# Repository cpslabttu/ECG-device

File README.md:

# ECG-device-TypeC
Created by: Dr. B. I. Morshed, Assoc. Prof., EECE, University of Memphis, Memphis TN USA.

If using this project files, please cite:

B. I. Morshed, "Ultra Low-power Inductively Coupled Wearable ECG Sensor Design with Inkjet Printed Dry Electrodes", National Radio Science Meeting, Boulder, CO, 2019.

B. I. Morshed, B. Harmon, M. S. Zaman, M. J. Rahman, S. Afroz, and M. Rahman, "Inkjet Printed Fully-passive Body-worn Wireless Sensors for Smart and Connected Community (SCC)", J. Low Power Electron. Appl., vol. 7, no. 4, article 26, pp. 1-21, Nov. 2017.

Sergi Consul-Pacareu, and Bashir I. Morshed, "Design and analysis of a novel wireless resistive analog passive sensor technique", IET Wireless Sensor Systems, vol. 8, no. 2, pp. 45-51, 2018.

B. Noroozi and B. I. Morshed, "PSC Optimization of 13.56-MHz Resistive Wireless Analog Passive Sensors", IEEE Trans. Microwave Theory and Techniques, vol. 65, no. 9, pp. 3548-3555, Sept. 2017.

For project related info, please visit: http://www.memphis.edu/esarp/nsf_scc/index.php

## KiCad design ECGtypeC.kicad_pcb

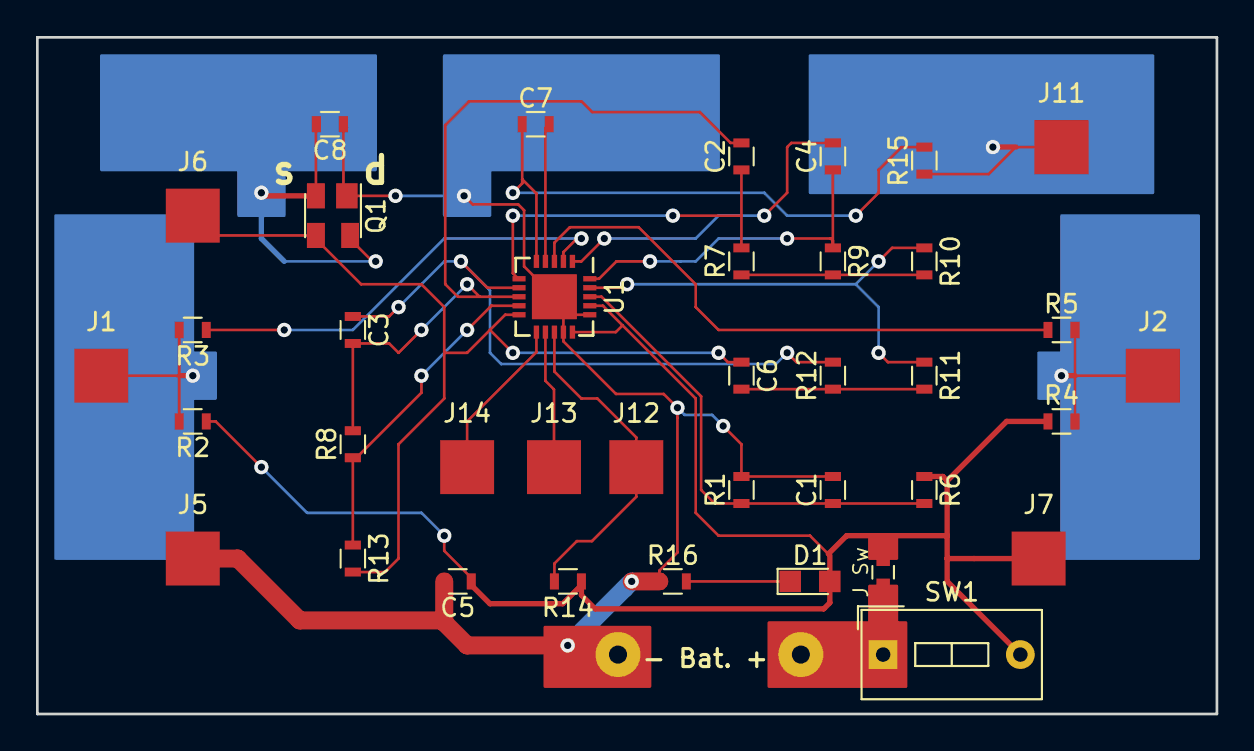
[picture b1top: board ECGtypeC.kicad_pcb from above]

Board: 2 copper layers, 65.5 x 37.6 mm, 39 parts (0 on the bottom side), 25 nets.

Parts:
- Bat. +: WireConnection_1mmDrill; WireConnection_1.00mmDrill
C1, C5: .1u; R_0603
C2, C4: .33u; R_0603
C3: 10n; R_0603
C6: .5n; R_0603
C7: 1n; R_0603
C8: 200p; R_0603
D1: LED_ALT; LED_0805
J1: L; Measurement_Point_Square-SMD-Pad_Big
J2: R; Measurement_Point_Square-SMD-Pad_Big
J5: Gnd; Measurement_Point_Square-SMD-Pad_Big
J6: Out; Measurement_Point_Square-SMD-Pad_Big
J7: Vdd; Measurement_Point_Square-SMD-Pad_Big
J11: D; Measurement_Point_Square-SMD-Pad_Big
J12: SDN; Measurement_Point_Square-SMD-Pad_Big
J13: LO+; Measurement_Point_Square-SMD-Pad_Big
J14: LO-; Measurement_Point_Square-SMD-Pad_Big
J Sw: C_0603_HandSoldering
Q1: 3SK263; SOT-143
R1, R2, R4, R6, R9, R10: 10M; R_0603
R3, R5: 180k; R_0603
R7: 1.4M; R_0603
R8: 100k; R_0603
R11, R12, R13: 1M; R_0603
R14: 10k; R_0603
R15: 300k; R_0603
R16: 1k; R_0603
SW1: SW_DIP_x01; SW_DIP_x1_W7.62mm_Slide
U1: AD8232; QFN-20-1EP_4x4mm_Pitch0.5mm

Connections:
0: C1.2, C5.2, C8.1, J5.1, Q1.1, R1.2, R16.1, U1.14, U1.16, U1.21
/LO+: J13.1, U1.12
/LO-: J14.1, U1.11
/SDN: J12.1, R14.2, U1.13
unnamed: C1.1, R1.1, R6.2, U1.18
unnamed: C2.1, R7.2, U1.6
unnamed: C2.2, C3.2, R8.2, U1.8
unnamed: C3.1, R12.2, U1.7
unnamed: C4.1, R9.1, U1.20
unnamed: C4.2, U1.1
unnamed: C5.1, D1.2, J7.1, R2.1, R4.1, R6.1, R14.1, SW1.2, U1.15, U1.17
unnamed: C6.1, J6.1, Q1.3, R13.2, U1.10
unnamed: C6.2, R11.2, R12.1
unnamed: C7.1, R15.2, U1.5
unnamed: C7.2, U1.4
unnamed: C8.2, Q1.2, Q1.4
unnamed: D1.1, R16.2
unnamed: J1.1, R2.2, R3.2
unnamed: J2.1, R4.2, R5.2
unnamed: J11.1, R15.1
unnamed: R3.1, U1.2
unnamed: R5.1, U1.3
unnamed: R10.1, R11.1, U1.19
unnamed: R7.1, R9.2, R10.2
unnamed: R8.1, R13.1, U1.9

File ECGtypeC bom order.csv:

Reference, Value, Footprint, DatasheetU1,AD8232ACPZ-R7,Housings_DFN_QFN:QFN-20-1EP_4x4mm_Pitch0.5mm,SW1,SW_DIP_x01,Buttons_Switches_THT:SW_DIP_x1_W7.62mm_Slide,C4,.33u,Resistors_SMD:R_0603,C3,10n,Resistors_SMD:R_0603,R9,10M,Resistors_SMD:R_0603,R7,1.4M,Resistors_SMD:R_0603,R10,10M,Resistors_SMD:R_0603,C2,.33u,Resistors_SMD:R_0603,R8,100k,Resistors_SMD:R_0603,R13,1M,Resistors_SMD:R_0603,C6,.5n,Resistors_SMD:R_0603,R12,1M,Resistors_SMD:R_0603,R11,1M,Resistors_SMD:R_0603,R6,10M,Resistors_SMD:R_0603,C5,.1u,Resistors_SMD:R_0603,C1,.1u,Resistors_SMD:R_0603,R1,10M,Resistors_SMD:R_0603,R14,10k,Resistors_SMD:R_0603,R2,10M,Resistors_SMD:R_0603,R4,10M,Resistors_SMD:R_0603,R15,300k,Resistors_SMD:R_0603,R3,180k,Resistors_SMD:R_0603,R5,180k,Resistors_SMD:R_0603,C7,1n,Resistors_SMD:R_0603,Q1,3SK263,TO_SOT_Packages_SMD:SOT-143,http://www.onsemi.com/pub_link/Collateral/EN4423-D.PDFC8,200p,Resistors_SMD:R_0603,R16,1k,Resistors_SMD:R_0603,D1,LED_ALT,LEDs:LED_0805,J3,L,,J4,R,,J8,D,,J9,Coil0,,J10,Coil1,,J5,Gnd,Measurement_Points:Measurement_Point_Square-SMD-Pad_Big,J7,Vdd,Measurement_Points:Measurement_Point_Square-SMD-Pad_Big,J6,Out,Measurement_Points:Measurement_Point_Square-SMD-Pad_Big,J1,L,Measurement_Points:Measurement_Point_Square-SMD-Pad_Big,J2,R,Measurement_Points:Measurement_Point_Square-SMD-Pad_Big,J11,D,Measurement_Points:Measurement_Point_Square-SMD-Pad_Big,BT1,Battery_Cell,Connectors:CR2032V,J12,SDN,Measurement_Points:Measurement_Point_Square-SMD-Pad_Big,J13,LO+,Measurement_Points:Measurement_Point_Square-SMD-Pad_Big,J14,LO-,Measurement_Points:Measurement_Point_Square-SMD-Pad_Big,
